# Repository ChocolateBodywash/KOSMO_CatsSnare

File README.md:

## KOSMO Format Cats Snare
### An 808 Style Snare

A KOSMO format module of a 808 Style Snare

I wanted a 808 style snare, but I also wanted it to be as simple as possible (no accent, pitch cv, etc) so I blended two simple schematics together. 

I used the tone section from the N8 808 Snare:
https://www.n8synth.co.uk/diy-eurorack/eurorack-808-snare

And the Noise section from Mortiz Kleins 808 Style Snare:
https://www.youtube.com/watch?v=hULEn2_4Unw

I like how the N8 tone blends two tone generators, it's pretty close to the original 808 schematic.
The noise from the Mortiz klein design I find to be simple, punchy and awesome.

I'm not 100% sure if I mixed the two properly, but I think the result is good enough for me.

---
Note: This was created by a hobbyist with no formal engineering training outside various late night YouTube binges. 
I’ve confirmed these designs to work but I make no guarantees on the design working efficiently.. or working at all.

Additional credit: Analog Output (Richard Holmes) for footprint libraries and front panel templates.

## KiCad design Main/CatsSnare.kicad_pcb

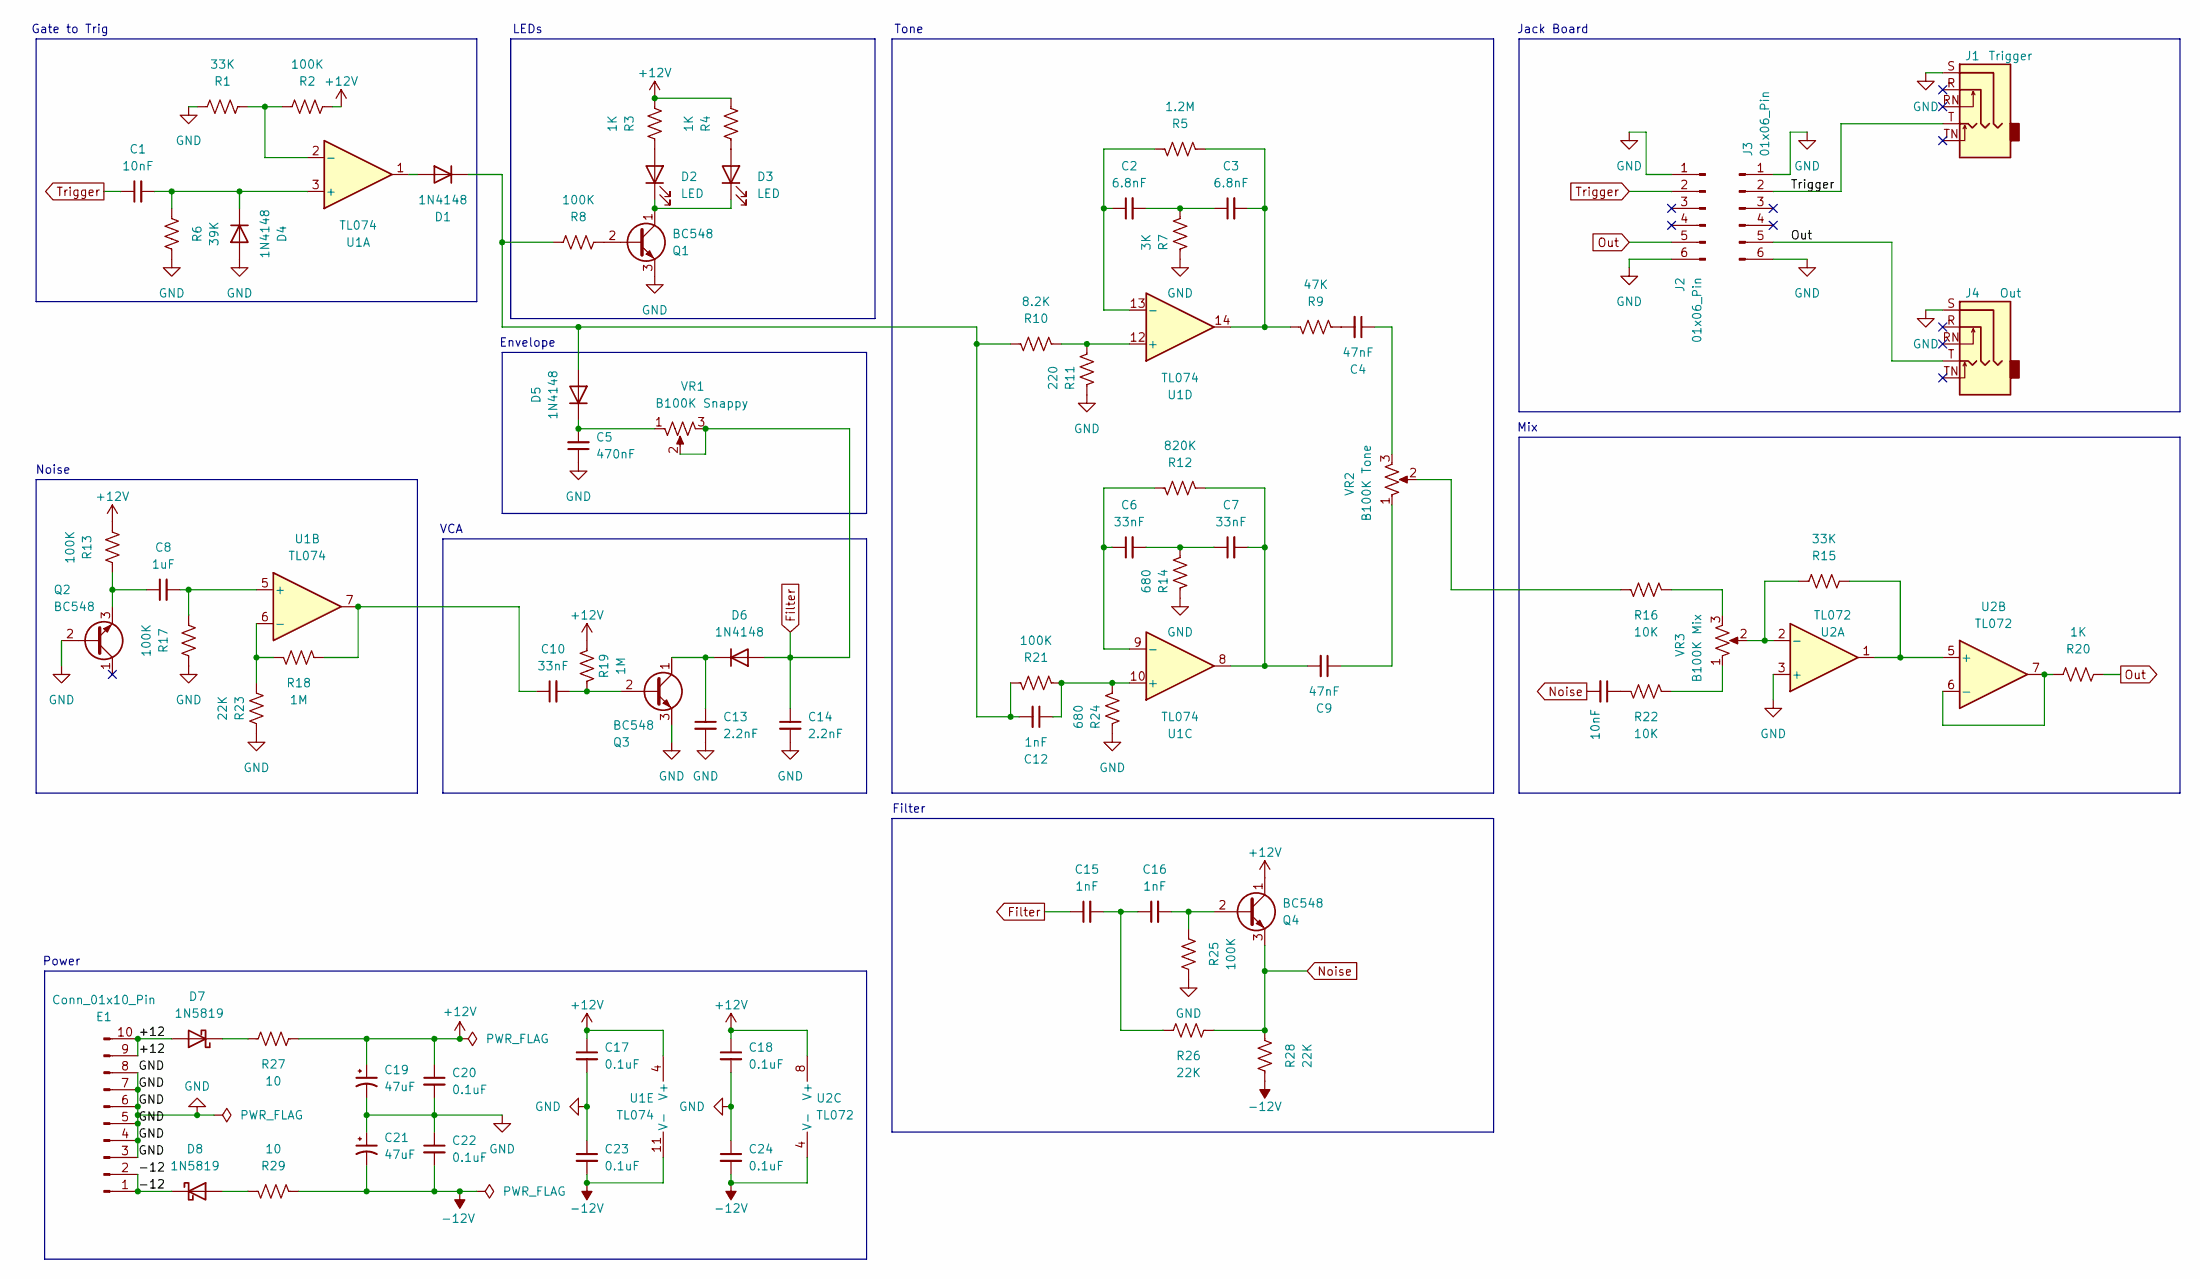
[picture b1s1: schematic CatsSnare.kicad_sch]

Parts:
C1, C11: 10nF; C_Rect_L7.0mm_W2.5mm_P5.00mm
C2, C3: 6.8nF; C_Rect_L7.0mm_W2.5mm_P5.00mm
C4, C9: 47nF; C_Rect_L7.0mm_W2.5mm_P5.00mm
C5: 470nF; C_Rect_L7.0mm_W2.5mm_P5.00mm
C6, C7, C10: 33nF; C_Rect_L7.0mm_W2.5mm_P5.00mm
C8: 1uF; C_Rect_L7.2mm_W5.5mm_P5.00mm_FKS2_FKP2_MKS2_MKP2
C12, C15, C16: 1nF; C_Rect_L7.0mm_W2.5mm_P5.00mm
C13, C14: 2.2nF; C_Rect_L7.0mm_W2.5mm_P5.00mm
C17, C18, C20, C22, C23, C24: 0.1uF; C_Disc_D3.0mm_W1.6mm_P2.50mm
C19, C21: 47uF; CP_Radial_D5.0mm_P2.50mm
D1, D4, D5, D6: 1N4148; D_DO-35_SOD27_P7.62mm_Horizontal
D2, D3: LED; LED_D5.0mm
D7, D8: 1N5819; D_DO-41_SOD81_P10.16mm_Horizontal
E1: Conn_01x10_Pin; Pins_2x05_2.54mm_TH_EurorackPower_Shrouded
J1: Trigger; Jack_6.35mm_PJ_629HAN
J2, J3: 01x06_Pin; PinHeader_1x06_P2.54mm_Vertical_Centered
J4: Out; Jack_6.35mm_PJ_629HAN
Q1, Q2, Q3, Q4: BC548; TO-92_Inline_Wide
R1, R15: 33K; R_Axial_DIN0207_L6.3mm_D2.5mm_P10.16mm_Horizontal
R2, R8, R13, R17, R21, R25: 100K; R_Axial_DIN0207_L6.3mm_D2.5mm_P10.16mm_Horizontal
R3, R4, R20: 1K; R_Axial_DIN0207_L6.3mm_D2.5mm_P10.16mm_Horizontal
R5: 1.2M; R_Axial_DIN0207_L6.3mm_D2.5mm_P10.16mm_Horizontal
R6: 39K; R_Axial_DIN0207_L6.3mm_D2.5mm_P10.16mm_Horizontal
R7: 3K; R_Axial_DIN0207_L6.3mm_D2.5mm_P10.16mm_Horizontal
R9: 47K; R_Axial_DIN0207_L6.3mm_D2.5mm_P10.16mm_Horizontal
R10: 8.2K; R_Axial_DIN0207_L6.3mm_D2.5mm_P10.16mm_Horizontal
R11: 220; R_Axial_DIN0207_L6.3mm_D2.5mm_P10.16mm_Horizontal
R12: 820K; R_Axial_DIN0207_L6.3mm_D2.5mm_P10.16mm_Horizontal
R14, R24: 680; R_Axial_DIN0207_L6.3mm_D2.5mm_P10.16mm_Horizontal
R16, R22: 10K; R_Axial_DIN0207_L6.3mm_D2.5mm_P10.16mm_Horizontal
R18, R19: 1M; R_Axial_DIN0207_L6.3mm_D2.5mm_P10.16mm_Horizontal
R23, R26, R28: 22K; R_Axial_DIN0207_L6.3mm_D2.5mm_P10.16mm_Horizontal
R27, R29: 10; R_Axial_DIN0207_L6.3mm_D2.5mm_P10.16mm_Horizontal
U1: TL074; DIP-14_W7.62mm_Socket_LongPads
U2: TL072; DIP-8_W7.62mm_Socket_LongPads
VR1: B100K Snappy; Potentiometer_Alpha_RD901F-40-00D_Single_Vertical
VR2: B100K Tone; Potentiometer_Alpha_RD901F-40-00D_Single_Vertical
VR3: B100K Mix; Potentiometer_Alpha_RD901F-40-00D_Single_Vertical

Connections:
+12V: C17.1, C18.1, C19.1, C20.1, Q4.1 (C), R2.1, R3.1, R4.1, R13.1, R19.1, R27.2, U1.4 (V+), U2.8 (V+)
-12V: C21.2, C22.2, C23.2, C24.2, R28.1, R29.2, U1.11 (V-), U2.4 (V-)
/+12: D7.2 (A), E1.9, E1.10
/-12: D8.1 (K), E1.1, E1.2
Filter: C14.1, C15.1, D6.2 (A), VR1.2, VR1.3
GND: C5.1, C13.2, C14.2, C17.2, C18.2, C19.2, C20.2, C21.1, C22.1, C23.1, C24.1, D4.2 (A), E1.3, E1.4, E1.5, E1.6, E1.7, E1.8, J1.S, J2.1, J2.6, J3.1, J3.6, J4.S, Q1.3 (E), Q2.2 (B), Q3.3 (E), R1.2, R6.1, R7.1, R11.1, R14.1, R17.2, R23.2, R24.1, R25.1, U2.3 (+)
unnamed: C2.2, C3.1, R7.2
unnamed: C3.2, R5.2, R9.1, U1.14
unnamed: C4.1, VR2.3
unnamed: C4.2, R9.2
unnamed: C6.2, C7.1, R14.2
unnamed: C7.2, C9.2, R12.2, U1.8
unnamed: C9.1, VR2.1
unnamed: C10.1, R18.1, U1.7
unnamed: C11.1, R22.2
unnamed: C15.2, C16.1, R26.1
unnamed: D1.2 (A), U1.1
unnamed: C12.2, D1.1 (K), D5.2 (A), R8.2, R10.1, R21.1
unnamed: D2.2 (A), R3.2
unnamed: D2.1 (K), D3.1 (K), Q1.1 (C)
unnamed: D3.2 (A), R4.2
unnamed: C1.2, D4.1 (K), R6.2, U1.3 (+)
unnamed: C5.2, D5.1 (K), VR1.1
unnamed: C13.1, D6.1 (K), Q3.1 (C)
unnamed: D7.1 (K), R27.1
unnamed: D8.2 (A), R29.1
unnamed: Q1.2 (B), R8.1
unnamed: C8.1, Q2.3 (E), R13.2
unnamed: C10.2, Q3.2 (B), R19.2
unnamed: C16.2, Q4.2 (B), R25.2
unnamed: R16.1, VR3.3
unnamed: R16.2, VR2.2
unnamed: R22.1, VR3.1
unnamed: R1.1, R2.2, U1.2 (-)
unnamed: C8.2, R17.1, U1.5 (+)
unnamed: R18.2, R23.1, U1.6 (-)
unnamed: C12.1, R21.2, R24.2, U1.10 (+)
unnamed: C6.1, R12.1, U1.9 (-)
unnamed: R10.2, R11.2, U1.12 (+)
unnamed: C2.1, R5.1, U1.13 (-)
unnamed: R15.2, U2.2 (-), VR3.2
unnamed: R15.1, U2.1, U2.5 (+)
unnamed: R20.2, U2.6 (-), U2.7
Noise: C11.2, Q4.3 (E), R26.2, R28.2
Out: J2.5, J3.5, J4.T, R20.1
Trigger: C1.1, J1.T, J2.2, J3.2

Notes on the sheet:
VCA
Filter
Power
Gate to Trig
Noise
Tone
LEDs
Envelope
Jack Board
Mix

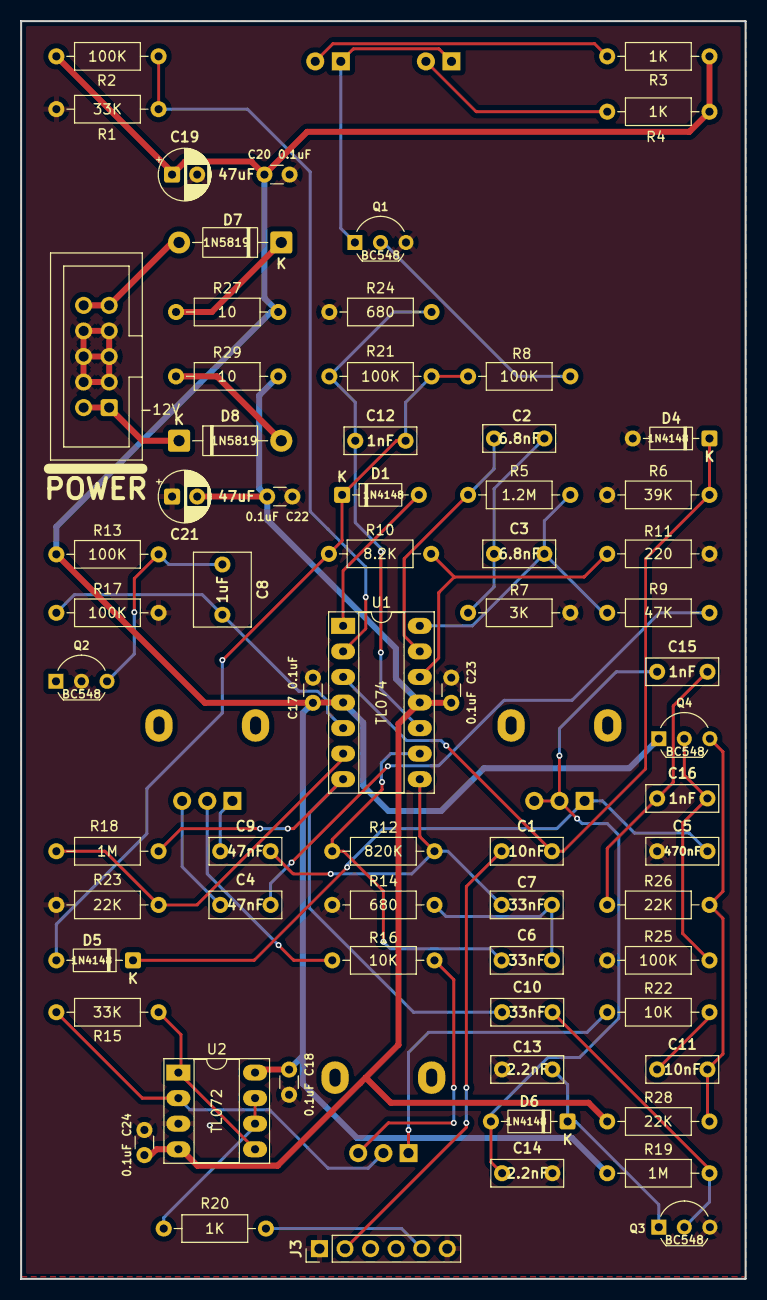
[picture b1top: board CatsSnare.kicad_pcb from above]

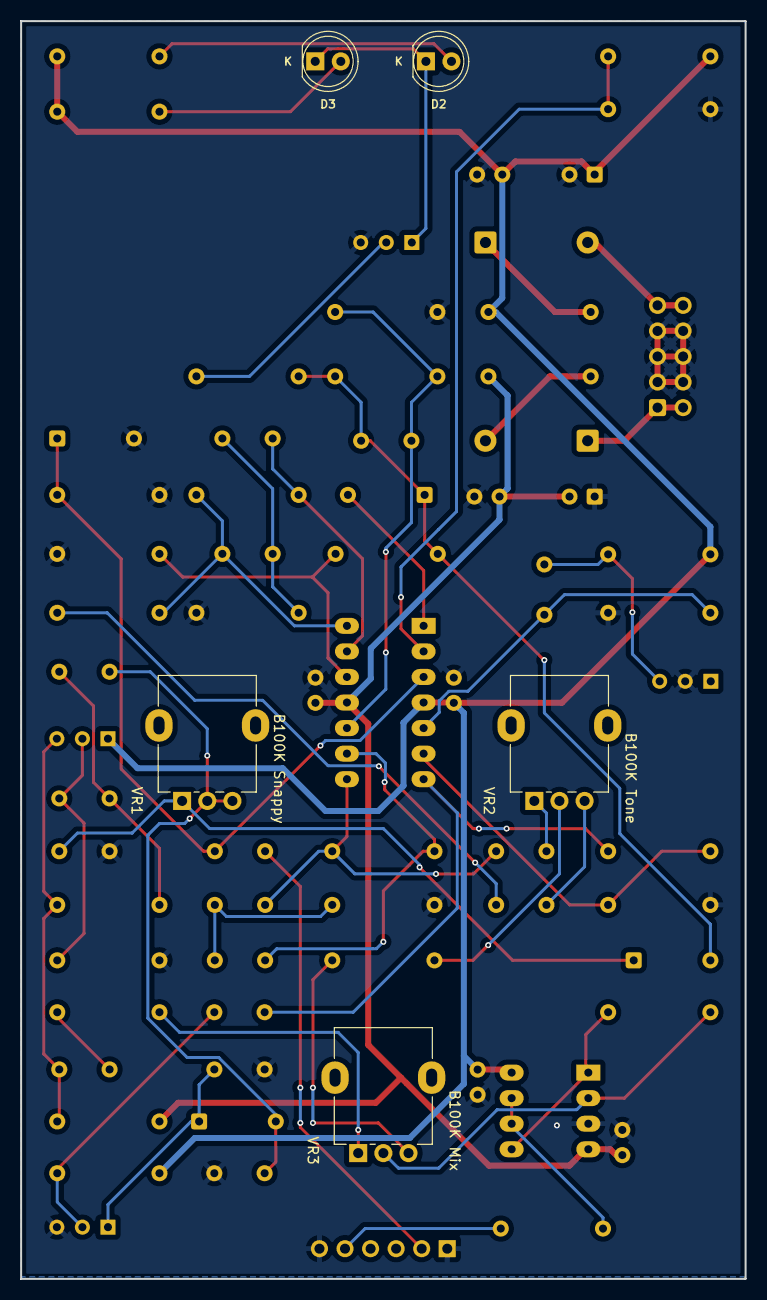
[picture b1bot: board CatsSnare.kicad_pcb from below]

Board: 2 copper layers, 72.0 x 125.0 mm, 72 parts (5 on the bottom side), 46 nets.
